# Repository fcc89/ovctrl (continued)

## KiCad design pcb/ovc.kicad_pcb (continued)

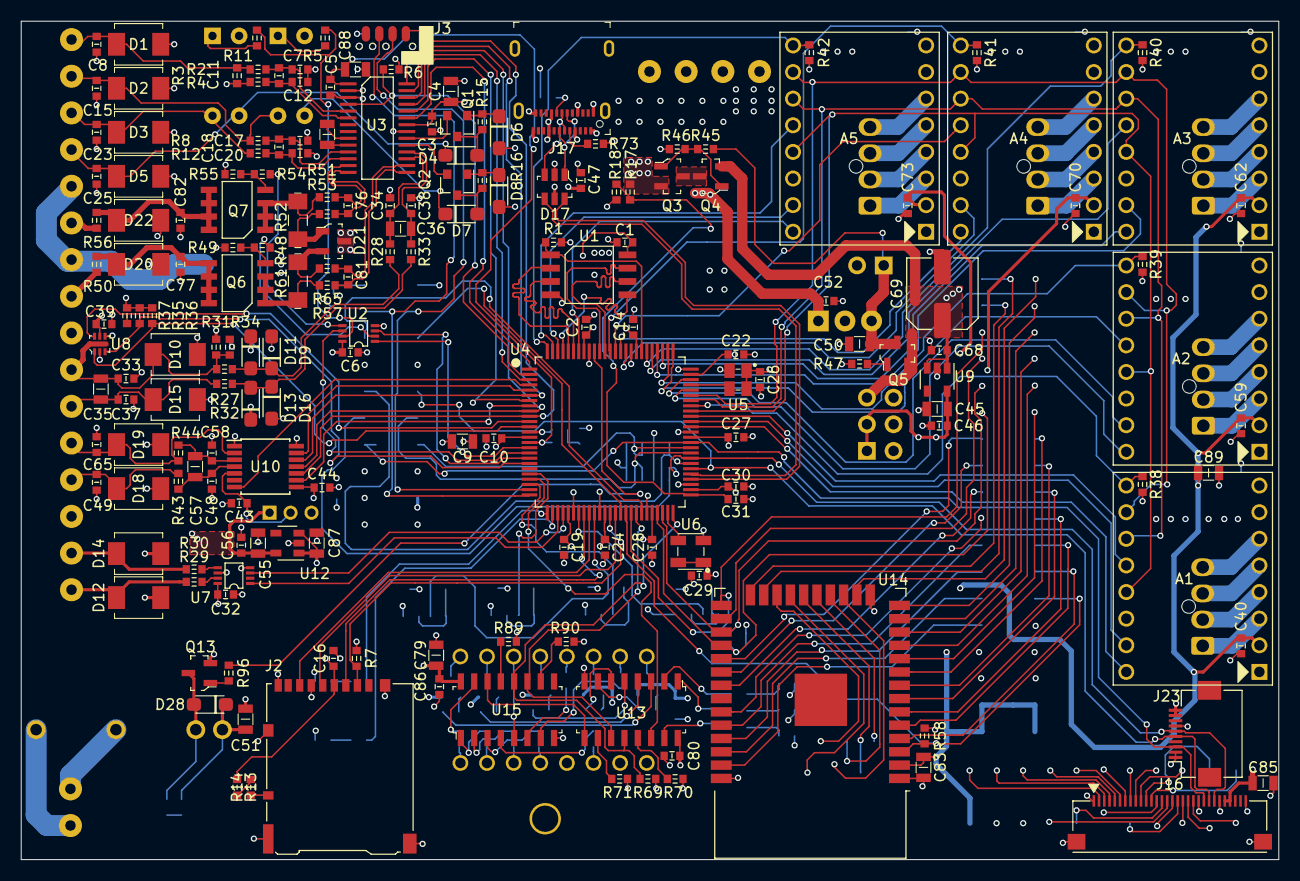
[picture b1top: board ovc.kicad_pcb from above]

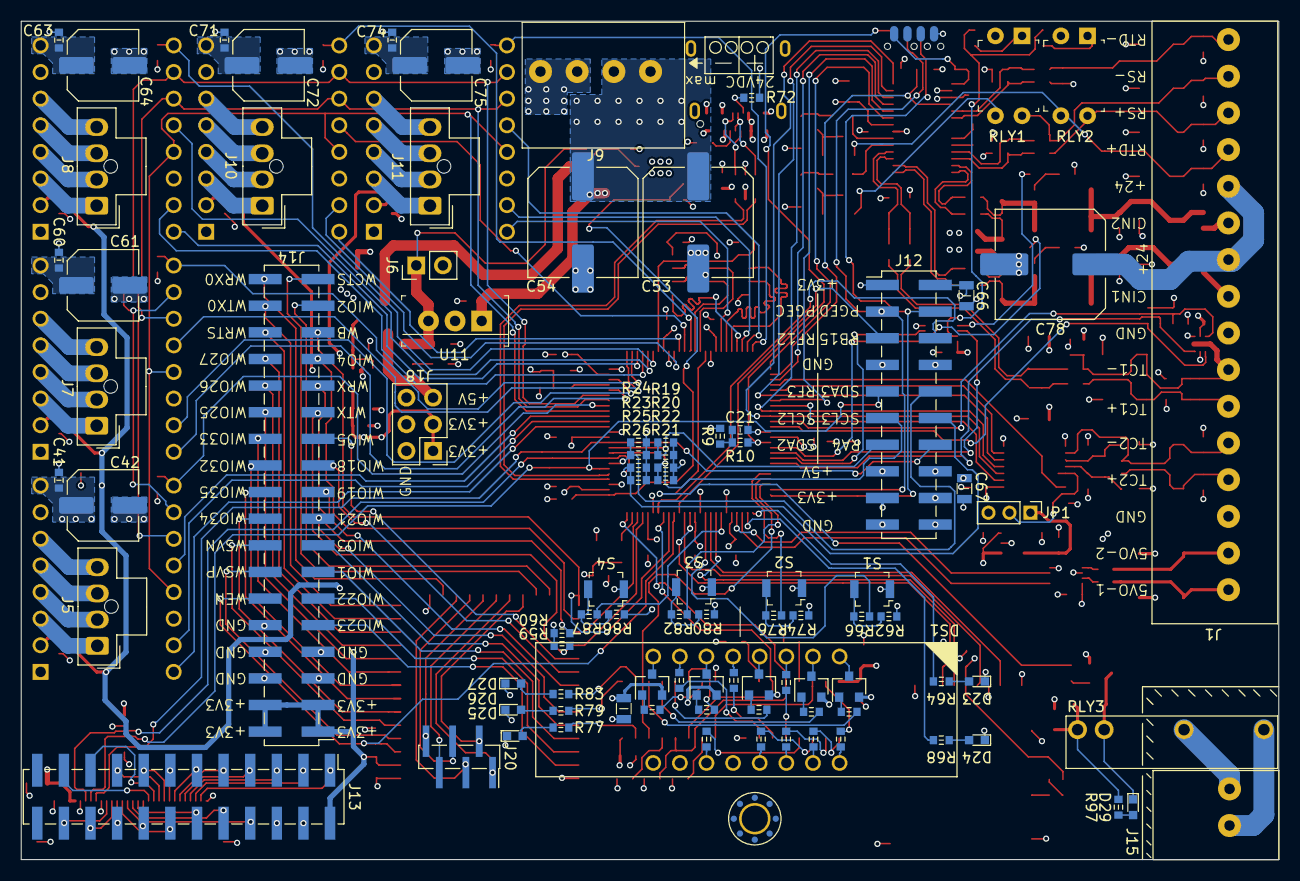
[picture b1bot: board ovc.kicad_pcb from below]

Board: 4 copper layers, 120.0 x 80.0 mm, 276 parts (92 on the bottom side), 271 nets.

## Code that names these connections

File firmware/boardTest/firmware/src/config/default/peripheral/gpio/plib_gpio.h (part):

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#define RTD_3W_OutputEnable()      (TRISGCLR = (1<<9))
#define RTD_3W_InputEnable()       (TRISGSET = (1<<9))
#define RTD_3W_PIN                  GPIO_PIN_RG9
/*** Macros for ICH1_EN pin ***/
#define ICH1_EN_Set()               (LATASET = (1<<0))
#define ICH1_EN_Clear()             (LATACLR = (1<<0))
#define ICH1_EN_Toggle()            (LATAINV= (1<<0))
#define ICH1_EN_Get()               ((PORTA >> 0) & 0x1)
#define ICH1_EN_OutputEnable()      (TRISACLR = (1<<0))
#define ICH1_EN_InputEnable()       (TRISASET = (1<<0))
#define ICH1_EN_PIN                  GPIO_PIN_RA0
/*** Macros for ICH2_EN pin ***/
#define ICH2_EN_Set()               (LATESET = (1<<8))
#define ICH2_EN_Clear()             (LATECLR = (1<<8))
#define ICH2_EN_Toggle()            (LATEINV= (1<<8))
#define ICH2_EN_Get()               ((PORTE >> 8) & 0x1)
#define ICH2_EN_OutputEnable()      (TRISECLR = (1<<8))
#define ICH2_EN_InputEnable()       (TRISESET = (1<<8))
#define ICH2_EN_PIN                  GPIO_PIN_RE8
/*** Macros for CJ_ALERT pin ***/
#define CJ_ALERT_Set()               (LATESET = (1<<9))
#define CJ_ALERT_Clear()             (LATECLR = (1<<9))
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#define SW3_OutputEnable()      (TRISBCLR = (1<<2))
#define SW3_InputEnable()       (TRISBSET = (1<<2))
#define SW3_PIN                  GPIO_PIN_RB2
/*** Macros for LED1 pin ***/
#define LED1_Set()               (LATBSET = (1<<6))
#define LED1_Clear()             (LATBCLR = (1<<6))
#define LED1_Toggle()            (LATBINV= (1<<6))
#define LED1_Get()               ((PORTB >> 6) & 0x1)
#define LED1_OutputEnable()      (TRISBCLR = (1<<6))
#define LED1_InputEnable()       (TRISBSET = (1<<6))
#define LED1_PIN                  GPIO_PIN_RB6
/*** Macros for LED2 pin ***/
#define LED2_Set()               (LATBSET = (1<<7))
#define LED2_Clear()             (LATBCLR = (1<<7))
#define LED2_Toggle()            (LATBINV= (1<<7))
#define LED2_Get()               ((PORTB >> 7) & 0x1)
#define LED2_OutputEnable()      (TRISBCLR = (1<<7))
#define LED2_InputEnable()       (TRISBSET = (1<<7))
#define LED2_PIN                  GPIO_PIN_RB7
/*** Macros for SW4 pin ***/
#define SW4_Set()               (LATBSET = (1<<8))
#define SW4_Clear()             (LATBCLR = (1<<8))
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#define SW1_OutputEnable()      (TRISBCLR = (1<<11))
#define SW1_InputEnable()       (TRISBSET = (1<<11))
#define SW1_PIN                  GPIO_PIN_RB11
/*** Macros for W_EN pin ***/
#define W_EN_Set()               (LATBSET = (1<<12))
#define W_EN_Clear()             (LATBCLR = (1<<12))
#define W_EN_Toggle()            (LATBINV= (1<<12))
#define W_EN_Get()               ((PORTB >> 12) & 0x1)
#define W_EN_OutputEnable()      (TRISBCLR = (1<<12))
#define W_EN_InputEnable()       (TRISBSET = (1<<12))
#define W_EN_PIN                  GPIO_PIN_RB12
/*** Macros for W_BOOT pin ***/
#define W_BOOT_Set()               (LATBSET = (1<<13))
#define W_BOOT_Clear()             (LATBCLR = (1<<13))
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
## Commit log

2019-09-27 base uppload
2019-09-29 added connections to ucontroller
2019-09-30 added memory pull ups connectors and memory ic
2019-10-01 sufriiiir
2019-10-04 finished schematic and starting location of components, advance in analog front end
2019-10-11 finished schematic, layed out components in pcb and advanced in routing
2019-10-29 gerber generated and fabricated
2019-11-24 Started module testing firmware
2019-11-24 Added PDF schematic and pcb
2019-12-19 advances in communication with pc
2020-01-03 advances in firmware
